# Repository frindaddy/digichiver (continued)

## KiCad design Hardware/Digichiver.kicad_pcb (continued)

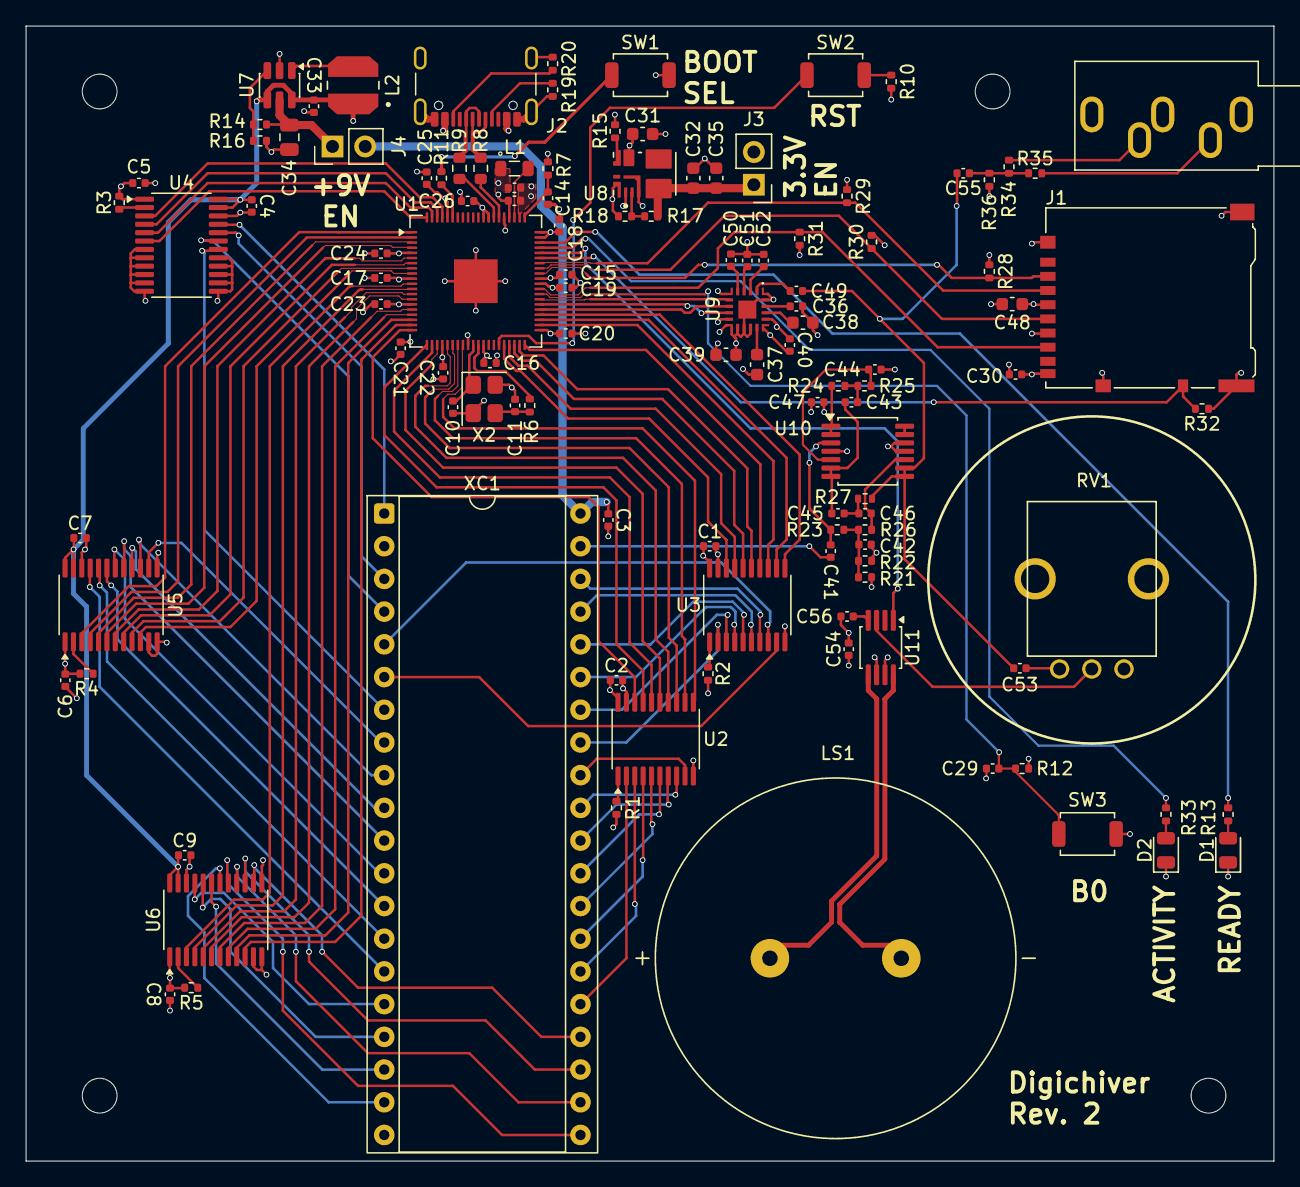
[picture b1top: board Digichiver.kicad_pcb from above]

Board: 4 copper layers, 96.9 x 88.1 mm, 121 parts (0 on the bottom side), 143 nets.

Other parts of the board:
MNT1, MNT2, MNT3, MNT4: MountingHole_2.7mm_M2.5

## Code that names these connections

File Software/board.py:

from machine import PWM, Pin

### Digitalker ###
# Explicit output values are required here: a pull-up does not define the
# output latch while the pin is in output mode.  Keep the Digitalker deselected
# and its write strobe inactive before its clock is enabled.
DIGITALKER_CS_N = Pin(1, Pin.OUT, value=1)
DIGITALKER_WR_N = Pin(2, Pin.OUT, value=1)
DIGITALKER_CMS = Pin(3, Pin.OUT, value=1)
SW = [Pin(i, Pin.OUT, value=0) for i in range(4, 12)]
DIGITALKER_CLK_4MHZ = PWM(Pin(0, Pin.OUT), freq=4_000_000)
DIGITALKER_CLK_4MHZ.duty_u16(0)
INTR = Pin(35, Pin.IN)

### ROM Emulator ###
ROM_ADDR = [Pin(i, Pin.IN) for i in range(20, 34)]
ROMEN_N = Pin(34, Pin.IN)
RDATA = [Pin(i, Pin.OUT) for i in range(12, 20)]

# I2S Bus
BCLK = Pin(36, Pin.OUT)
FSYNC = Pin(37, Pin.OUT)
SDATA = Pin(38, Pin.IN)

# microSD
SD_MISO = Pin(40, Pin.IN)
SD_CS_N = Pin(41, Pin.OUT)
SD_SCK = Pin(42, Pin.OUT)
SD_MOSI = Pin(43, Pin.OUT)
SD_DET = Pin(44, Pin.IN)

# GPIO
SPEAKER_DISABLE_N = Pin(45, Pin.OUT, value=0)
LED_ORANGE = Pin(46, Pin.OUT)
LED_GREEN = Pin(47, Pin.OUT)
BUTTON = Pin(39, Pin.IN)

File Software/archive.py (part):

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
@rp2.asm_pio(sideset_init=[rp2.PIO.OUT_LOW, rp2.PIO.OUT_LOW])
def _i2s_clock() -> None:
    """Generate 3.072 MHz BCLK and 48 kHz I2S FSYNC on two side-set pins.

    FSYNC low denotes the left slot.  It changes only with a falling BCLK edge
    and remains stable for a full bit clock before the slot's MSB, as I2S
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    """
    wrap_target()
    # asm_pio cannot resolve module globals inside a decorated program.  PIO2
    # GPIOBASE=16 maps operands 0..15 to physical GPIO32..47, so 5 is FSYNC
    # GPIO37 and 4 is BCLK GPIO36.
    wait(1, gpio, 5)
    wait(0, gpio, 5)
    wait(0, gpio, 4)
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
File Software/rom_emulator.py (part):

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ROM_ALIGNMENT = ROM_SIZE
RDATA_BASE = 12
ROM_ADDR_BASE = 20
ROMEN_GPIO = 34


def _dma_channel_base(channel: int) -> int:
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    # the last absolute address served and Y is the current address.
    wrap_target()
    label("idle")
    wait(0, gpio, 2)            # System GPIO34 with PIO GPIOBASE=16.
    mov(isr, osr)
    in_(pins, 14)               # GPIO20..33, relative to GPIO base 16.
    mov(x, isr)
    push(block)                 # Always serve the first address after ROMEN.

    label("active")
    jmp(pin, "idle")            # ROMEN high: wait for the next assertion.
    mov(isr, osr)
    in_(pins, 14)
    mov(y, isr)
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        # make its inactive value known until the first ROM transaction.
        for gpio in range(RDATA_BASE, RDATA_BASE + 8):
            Pin(gpio, Pin.OUT, value=0)
        for gpio in range(ROM_ADDR_BASE, ROMEN_GPIO + 1):
            Pin(gpio, Pin.IN)

        # PIO0 handles GPIO12..19 with base 0.  PIO1 handles GPIO20..34 with
        # base 16, allowing both the 14-bit address bus and ROMEN in one SM.
        mem32[PIO0_BASE + PIO_GPIOBASE] = 0
        mem32[PIO1_BASE + PIO_GPIOBASE] = 16
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        )
        self._capture_sm = rp2.StateMachine(
            4, _capture_request, freq=150_000_000,
            in_base=Pin(ROM_ADDR_BASE), jmp_pin=Pin(ROMEN_GPIO)
        )

        self._configure_dma()
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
